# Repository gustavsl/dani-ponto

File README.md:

# dani-ponto
Sistema de relógio de ponto eletrônico

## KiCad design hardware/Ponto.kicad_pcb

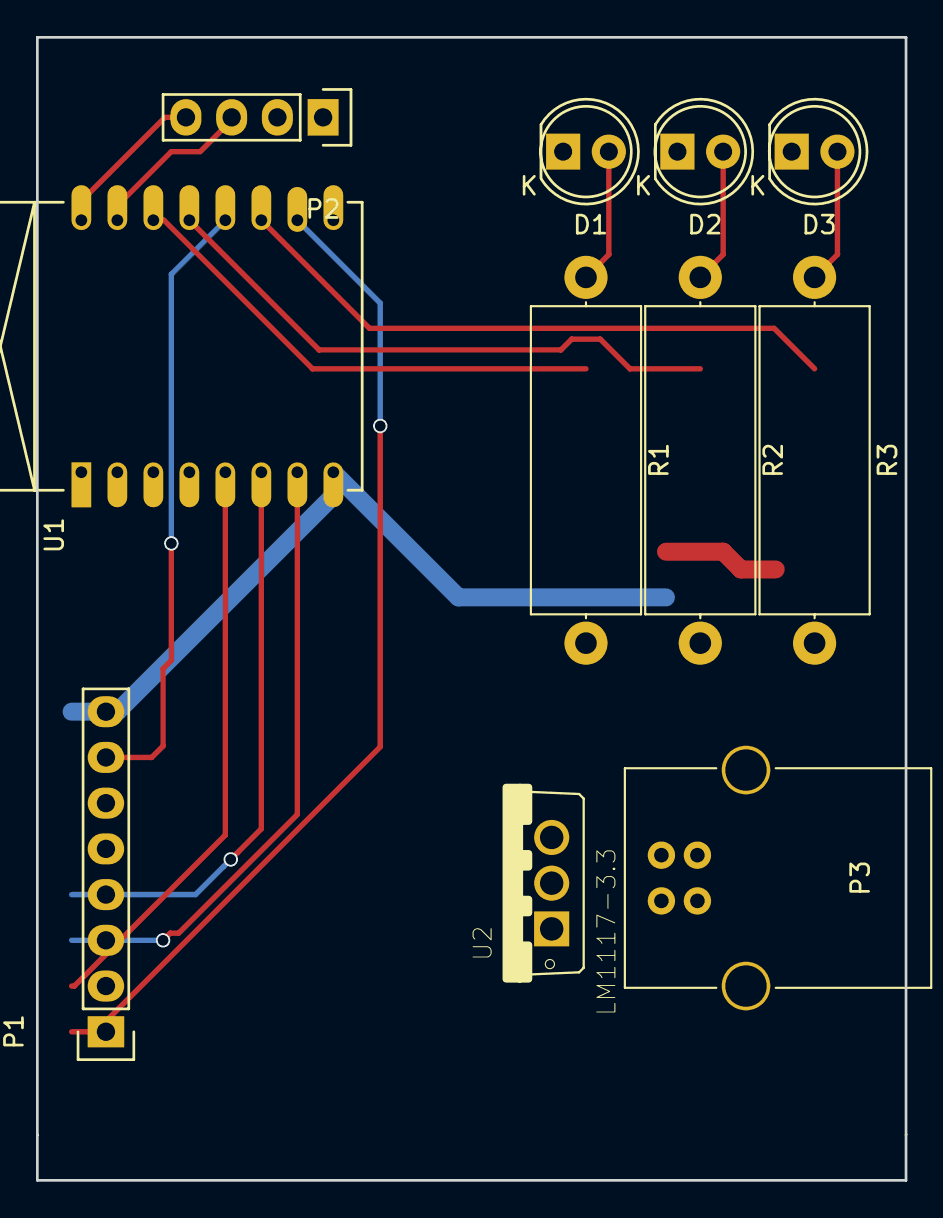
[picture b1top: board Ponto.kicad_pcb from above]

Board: 2 copper layers, 48.3 x 63.5 mm, 11 parts (0 on the bottom side), 16 nets.

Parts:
D1, D2, D3: LED; LED-5MM
P1: RFID-RC522-MODULE; Socket_Strip_Straight_1x08
P2: CONN_01X04; Socket_Strip_Straight_1x04
P3: USB_B
R1, R2, R3: 4K7; R_Axial_DIN0617_L17.0mm_D6.0mm_P20.32mm_Horizontal
U1: ESP-07v2
U2: LM1117-3.3; TO-220-3

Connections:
GND: D1.1, D2.1, D3.1, P1.6, P2.2, P3.4, P3.5, U1.9, U2.1
MISO: P1.4, U1.6
MOSI: P1.3, U1.7
unnamed: D1.2, R1.1
unnamed: D2.2, R2.1
unnamed: D3.2, R3.1
unnamed: P3.1, U2.3
unnamed: R1.2, U1.14
unnamed: R2.2, U1.13
unnamed: R3.2, U1.11
RST: P1.7, U1.12
RX: P2.3, U1.15
SCK: P1.2, U1.5
SDA: P1.1, U1.10
TX: P2.4, U1.16
VCC: P1.8, P2.1, U1.8, U2.2

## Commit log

2017-08-28 Iniciando desenvolvimento do hardware
2017-08-29 Começando PCB
2017-11-09 Organizando pastas
